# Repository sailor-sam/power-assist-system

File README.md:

# power-assist-system
Electronic servo motor system designed to assist people with severe  disabilities to control the helm and sail sheeting systems of a small  sailboat, via a sip&amp;puff or medical joystick interface.

Kevin and Rick Mercer

https://youtu.be/U6-sZrs9T38?si=PjePZXyoL59SkXcZ&t=115

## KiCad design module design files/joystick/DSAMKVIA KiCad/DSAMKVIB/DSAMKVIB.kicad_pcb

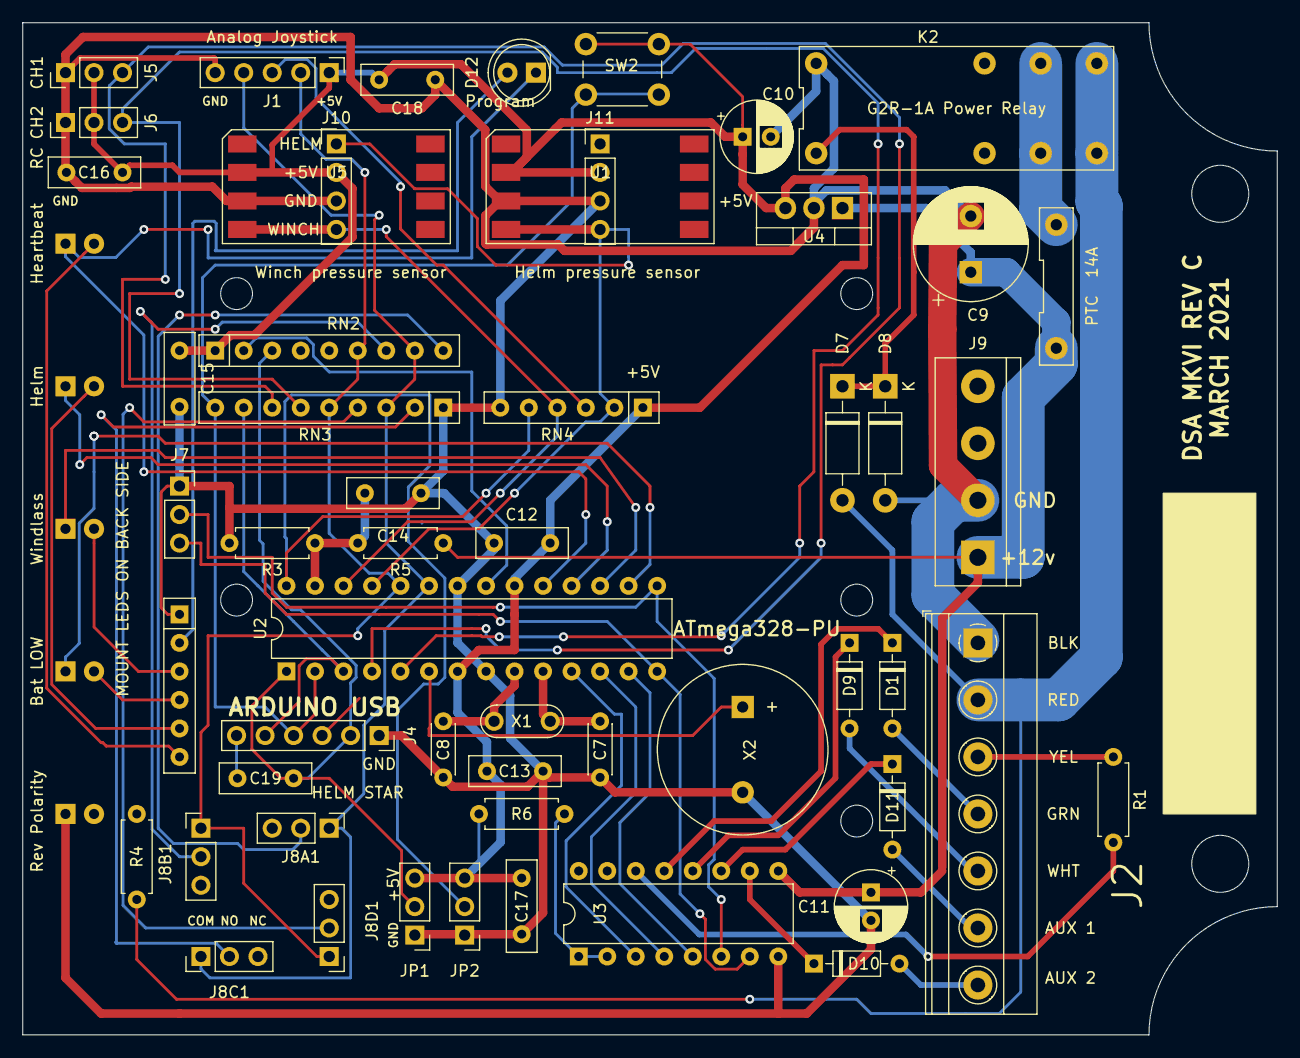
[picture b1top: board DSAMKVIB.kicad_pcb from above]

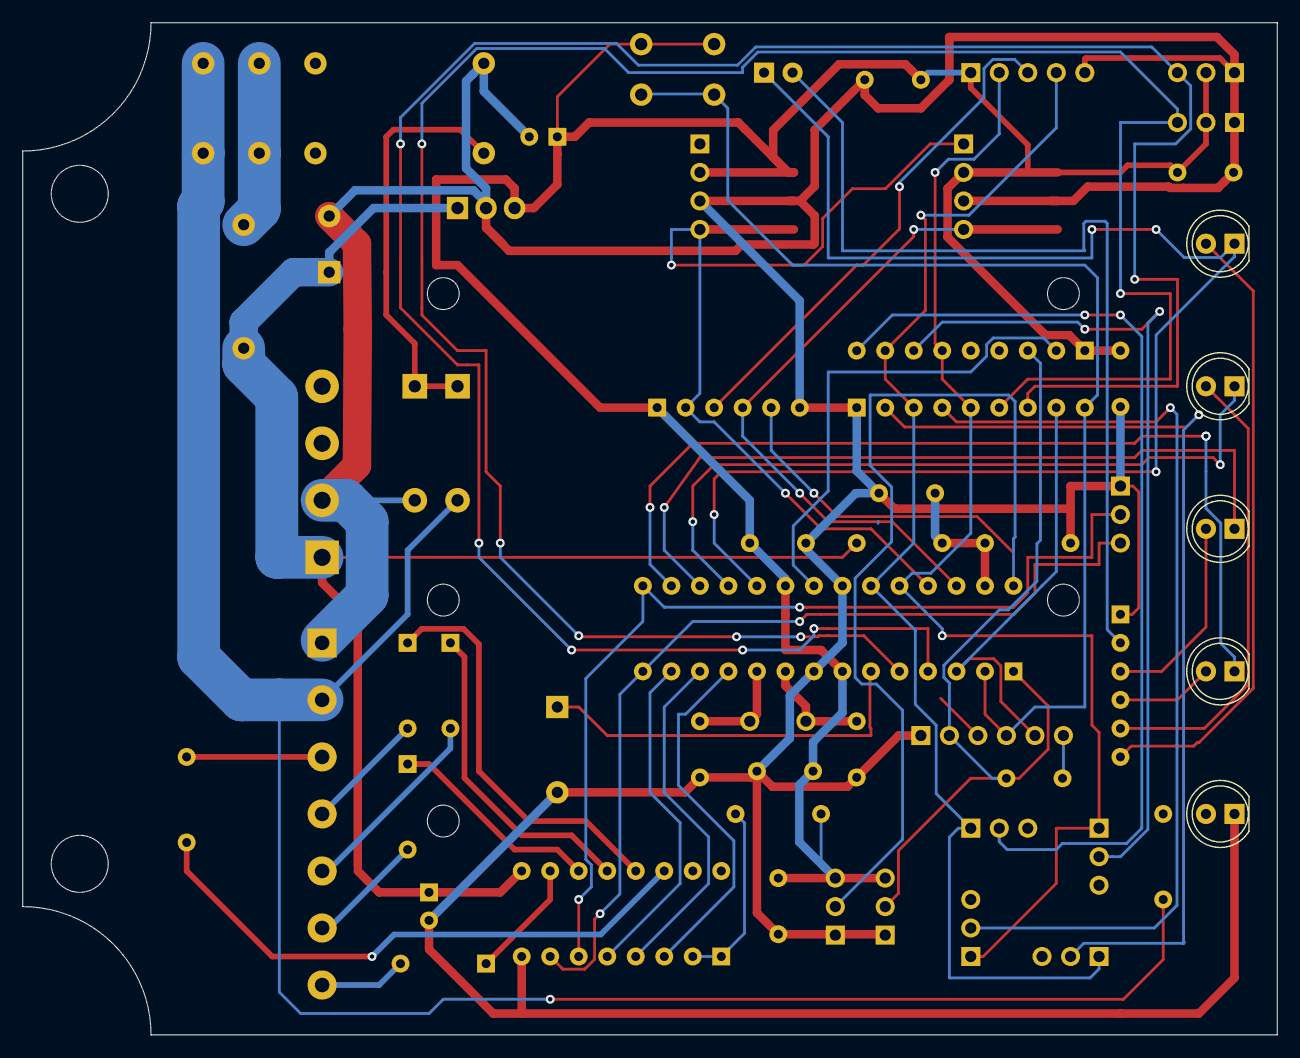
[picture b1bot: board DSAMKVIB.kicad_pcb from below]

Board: 2 copper layers, 111.8 x 90.2 mm, 59 parts (5 on the bottom side), 53 nets.

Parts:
C7, C8: 22 pF; C_Disc_D4.3mm_W1.9mm_P5.00mm
C9: 1000 uF 16V; CP_Radial_D10.0mm_P5.00mm
C10: 10 uF 16V; CP_Radial_D6.3mm_P2.50mm
C11: 10uF 16V; CP_Radial_D6.3mm_P2.50mm
C12, C13, C15, C16, C17, C18: .47uF 50V; C_Disc_D8.0mm_W2.5mm_P5.00mm
C14: 4N7; C_Disc_D8.0mm_W2.5mm_P5.00mm
C19: .1uF 50V; C_Disc_D8.0mm_W2.5mm_P5.00mm
D1, D9, D10, D11: BAT48RL; D_DO-35_SOD27_P7.62mm_Horizontal
D2: Heartbeat; LED_D5.0mm
D3: Helm; LED_D5.0mm
D4: Windlass; LED_D5.0mm
D5: Bat LOW; LED_D5.0mm
D6: Rev Polarity; LED_D5.0mm
D7, D8: 1N4001; D_DO-41_SOD81_P10.16mm_Horizontal
D12: Program LED; LED_D5.0mm
F1: PTC 14A; PTC14
J1: Analog Joystick; PinHeader_1x05_P2.54mm_Vertical
J2: .200 EURO; TerminalBlock_Phoenix_MKDS-1,5-7-5.08_1x07_P5.08mm_Horizont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
J4: USB; PinSocket_1x06_P2.54mm_Vertical
J5: CH1; PinHeader_1x03_P2.54mm_Vertical
J6: CH2; PinHeader_1x03_P2.54mm_Vertical
J7: Cytron PWM; PinSocket_1x03_P2.54mm_Vertical
J8A1: HELM STAR; PinHeader_1x03_P2.54mm_Vertical
J8B1: WINCH IN; PinHeader_1x03_P2.54mm_Vertical
J8C1: HELM PORT; PinHeader_1x03_P2.54mm_Vertical
J8D1: WINCH OUT; PinHeader_1x03_P2.54mm_Vertical
J9: Cytron Pwr; TerminalBlock_bornier-4_P5.08mm
J10: S&P WINCH; PinHeader_1x04_P2.54mm_Vertical
J11: S&P HELM; PinHeader_1x04_P2.54mm_Vertical
JP1: Jumper_CTS; PinHeader_1x03_P2.54mm_Vertical
JP2: Jumper_MODE; PinHeader_1x03_P2.54mm_Vertical
K2: G2R-1A Power Relay; G2R-1A
R1: 470R; R_Axial_DIN0207_L6.3mm_D2.5mm_P7.62mm_Horizontal
R3: 4.9K; R_Axial_DIN0207_L6.3mm_D2.5mm_P7.62mm_Horizontal
R4: 1K; R_Axial_DIN0207_L6.3mm_D2.5mm_P7.62mm_Horizontal
R5: 11K; R_Axial_DIN0207_L6.3mm_D2.5mm_P7.62mm_Horizontal
R6: 10K; R_Axial_DIN0207_L6.3mm_D2.5mm_P7.62mm_Horizontal
RN1: 470R; R_Array_SIP6
RN2, RN3: 10K; R_Array_SIP9
RN4: 100K DIVIDER; R_Array_SIP6
SW2: Program; SW_PUSH_6mm_H4.3mm
U1: Helm pressure sensor; MPXV7007
U2: ATmega328-PU; DIP-28_W7.62mm
U3: ULN2003; DIP-16_W7.62mm
U4: L7805; TO-220-3_Vertical
U5: Winch pressure sensor; MPXV7007
X1: 16 mhz xtal; Resonator-2Pin_W7.0mm_H2.5mm
X2: Buzzer; Buzzer_15x7.5RM7.6

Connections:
+5V: C10.1, C12.1, C13.1, C15.1, C16.1, C17.1, C18.1, J1.1, J4.3, J5.2, J6.2, J10.2, J11.2, JP1.3, JP2.3, R6.1, RN2.1, RN4.1, SW2.1, U1.2, U2.7, U2.20, U4.3, U5.2
+12V: C9.1, C11.1, F1.1, J9.1, R5.1, U3.9, U4.1
+BATT: D7.2, J2.2, K2.4, K2.5, R4.1
CH1: J5.3, RN3.7, U2.4
CH2: J6.3, RN3.6, U2.5
GNDREF: C7.2, C8.2, C9.2, C10.2, C11.2, C12.2, C13.2, C14.2, C15.2, C16.2, C17.2, C18.2, D6.1, D8.2, J1.5, J2.1, J4.1, J5.1, J6.1, J7.1, J9.2, J10.3, J11.3, JP1.1, JP2.1, K2.8, R3.2, RN1.1, RN3.1, RN4.6, U1.3, U2.8, U2.22, U3.8, U4.2, U5.3, X2.2
unnamed: C7.1, U2.10, X1.1
unnamed: C8.1, U2.9, X1.2
unnamed: C14.1, R3.1, R5.2, U2.27
unnamed: C19.1, J4.2, JP1.2, RN2.3, U2.1
unnamed: C19.2, J4.6
unnamed: D1.1, U3.13
unnamed: D1.2, J2.4
unnamed: D2.2, RN1.6
unnamed: D3.1, U2.18
unnamed: D3.2, RN1.5
unnamed: D4.1, U2.17
unnamed: D4.2, RN1.3
unnamed: D5.1, U2.16
unnamed: D5.2, RN1.4
unnamed: D6.2, R4.2
unnamed: D7.1, D8.1, K2.1
unnamed: D9.1, U3.12
unnamed: D9.2, J2.5
unnamed: D10.1, U3.10
unnamed: D10.2, J2.7
unnamed: D11.1, U3.11
unnamed: D11.2, J2.6
unnamed: D2.1, D12.1, U2.19
unnamed: D12.2, RN1.2
unnamed: F1.2, K2.3, K2.6
unnamed: J1.2, J8B1.1, J8D1.1, RN2.6, RN3.5, U2.24
unnamed: J1.3, RN4.3
unnamed: J1.4, J8A1.1, J8C1.1, RN2.8, RN3.3, U2.23
unnamed: J2.3, R1.1
unnamed: J4.4, RN3.9, SW2.2, U2.2
unnamed: J4.5, RN3.8, U2.3
unnamed: J7.2, U2.15, U3.6
unnamed: J7.3, U2.14, U3.7
unnamed: J8A1.2, RN2.9
unnamed: J8B1.2, RN2.7
unnamed: J8C1.2, RN3.2
unnamed: J8D1.2, RN3.4
unnamed: J10.1, J11.4, RN4.2, U1.4, U2.25
unnamed: J10.4, RN4.4, U2.26, U5.4
unnamed: JP2.2, RN4.5, U2.28
unnamed: R1.2, U3.14
unnamed: R6.2, U3.1, U3.2
unnamed: RN2.2, U2.21
unnamed: U2.6, X2.1
unnamed: U2.11, U3.3
unnamed: U2.12, U3.4
unnamed: U2.13, U3.5

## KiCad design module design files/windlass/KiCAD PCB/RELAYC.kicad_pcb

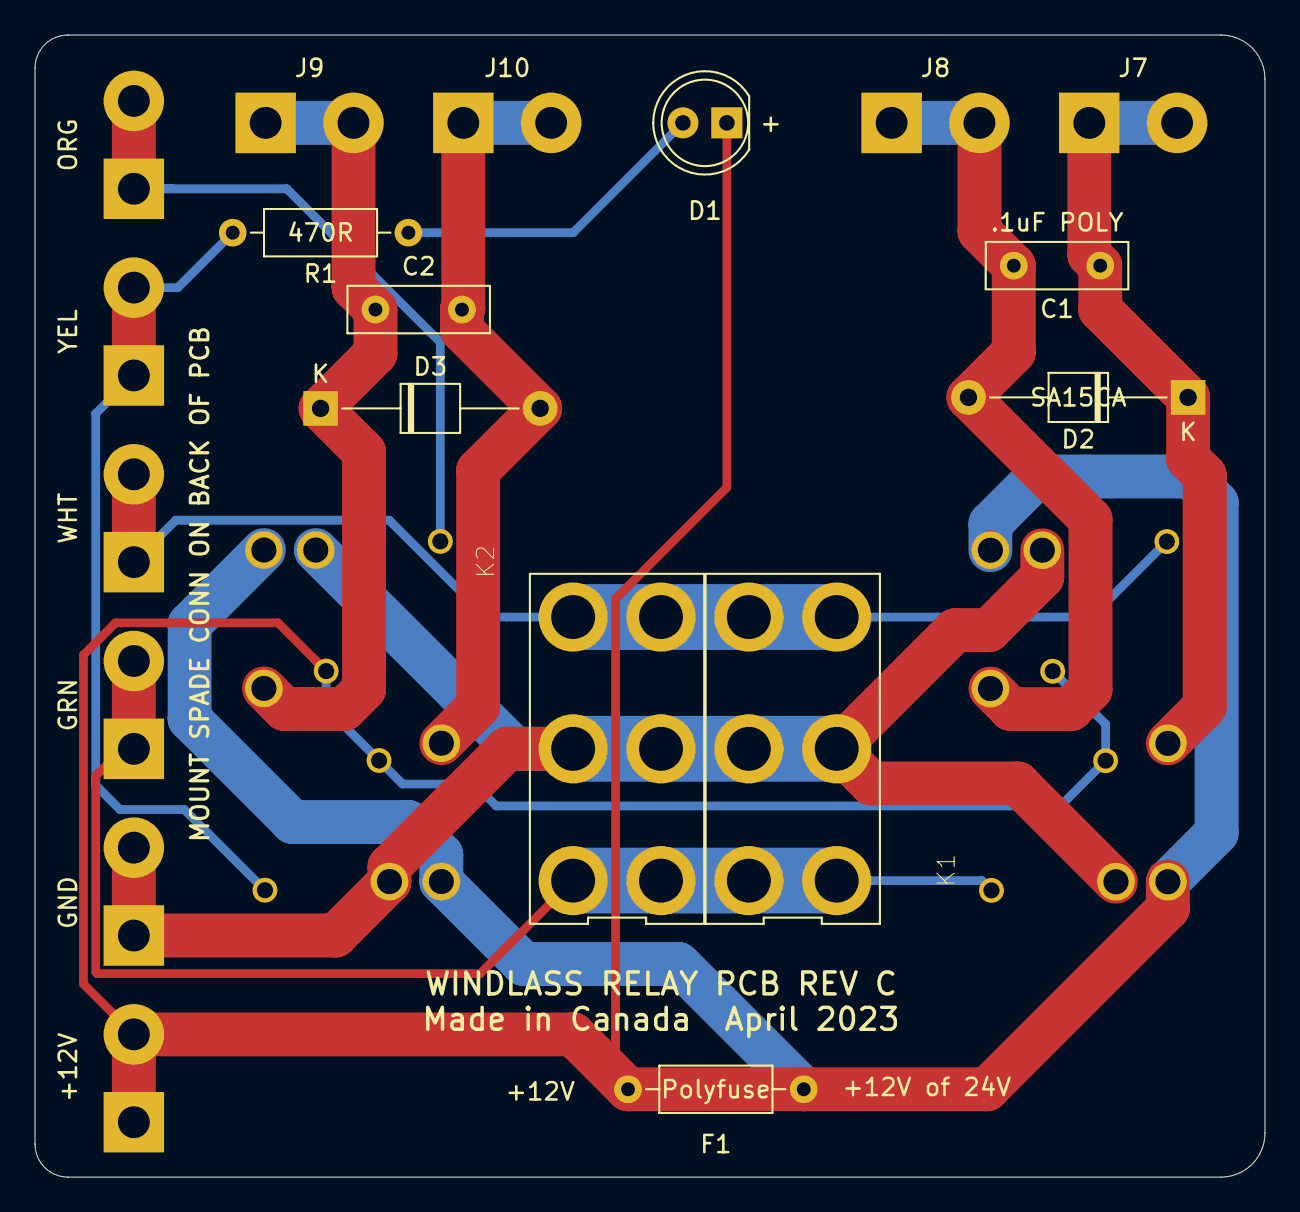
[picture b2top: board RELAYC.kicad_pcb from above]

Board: 2 copper layers, 71.1 x 66.0 mm, 21 parts (0 on the bottom side), 11 nets.

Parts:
C1, C2: .1uF POLY; C_Disc_D8.0mm_W2.5mm_P5.00mm
D1: LED; LED_D5.0mm
D2, D3: SA15CA; D_T-1_P12.70mm_Horizontal
F1: Polyfuse; R_Axial_DIN0207_L6.3mm_D2.5mm_P10.16mm_Horizontal
J1: +12V; 250spadeconn
J2: GND; 250spadeconn
J3: GRN; 250spadeconn
J4: WHT; 250spadeconn
J5: YEL; 250spadeconn
J6: ORG; 250spadeconn
J7, J9: A; 250spadeconn
J8, J10: B; 250spadeconn
K1, K2: V23086 relay; RELAY_V23086C2001A403
R1: 470R; R_Axial_DIN0207_L6.3mm_D2.5mm_P10.16mm_Horizontal
SW1, SW1B1: SW_DPDT_x2; DPDT_SW

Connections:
+12V: D1.1, F1.1, F1.2, J1.1, K1.11, K1.13, K1.21, K1.23, K2.11, K2.13, K2.21, K2.23
GNDREF: J2.1, K1.15, K1.25, K2.15, K2.25, SW1.2, SW1B1.2
unnamed: C1.1, D2.1, J7.1, K1.24
unnamed: C1.2, D2.2, J8.1, K1.14
unnamed: C2.1, D3.1, J9.1, K2.24
unnamed: C2.2, D3.2, J10.1, K2.14
unnamed: D1.2, R1.1
unnamed: J3.1, K1.22, SW1.1, SW1B1.1
unnamed: J4.1, K1.12, SW1.3, SW1B1.3
unnamed: J5.1, K2.12, R1.2
unnamed: J6.1, K2.22

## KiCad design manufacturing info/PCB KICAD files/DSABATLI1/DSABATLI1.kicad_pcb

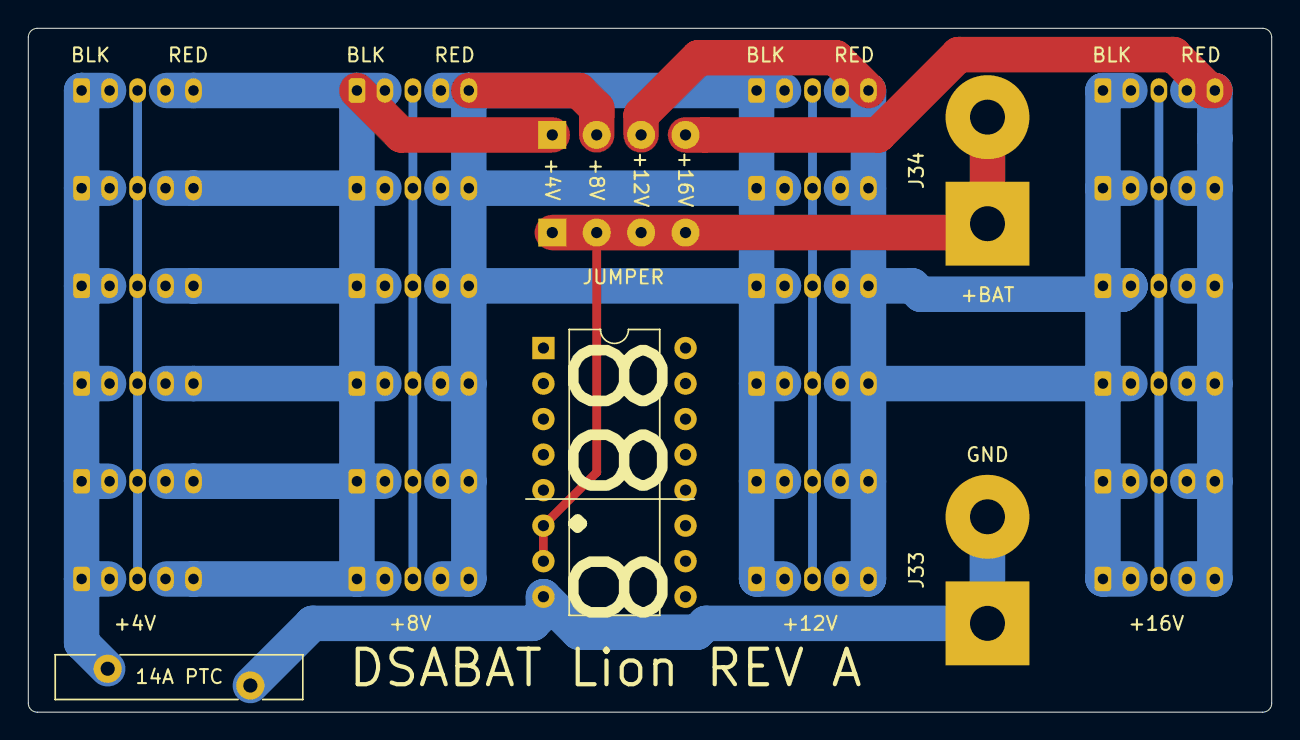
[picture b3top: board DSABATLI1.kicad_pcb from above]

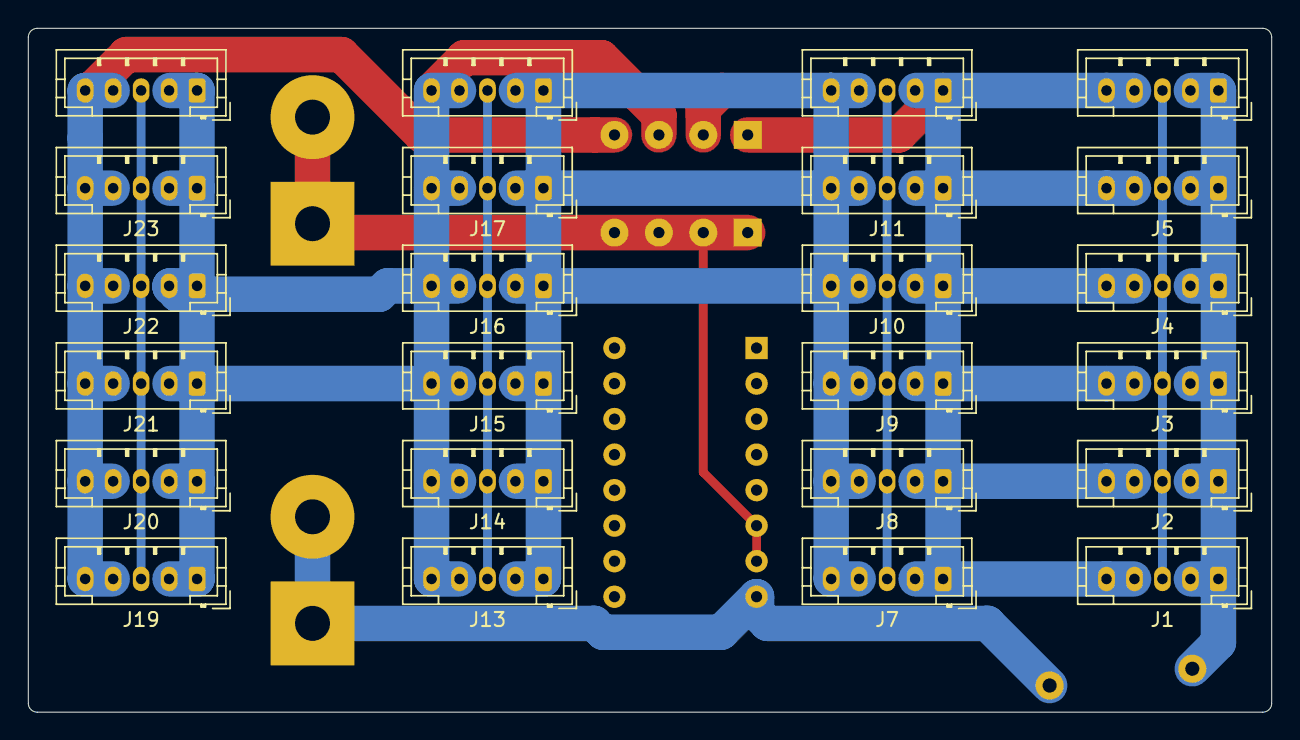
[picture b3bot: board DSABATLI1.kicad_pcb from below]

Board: 2 copper layers, 88.9 x 48.9 mm, 30 parts (24 on the bottom side), 11 nets.

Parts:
14A PTC: Polyfuse; Fuse_Bourns_MF-RHT1000
J1, J2, J3, J4, J5, J6, J7, J8, J9, J10, J11, J12, J13, J14, J15, J16, J17, J18, J19, J20, J21, J22, J23, J24: JST-PHR 5; JST_PH_B5B-PH-K_1x05_P2.00mm_Vertical
J30: .; SolderWirePad_1x04_P3.175mm_Drill0.8mm
J31: +bus; SolderWirePad_1x04_P3.175mm_Drill0.8mm
J33: GND; SolderWirePad_1x02_P7.62mm_Drill2.5mm
J34: +BAT; SolderWirePad_1x02_P7.62mm_Drill2.5mm
U1: VOLTMETER; DIP-16_W10.16mm

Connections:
unnamed: 14A PTC.1, J33.1, J33.2, U1.8
unnamed: 14A PTC.2, J1.1, J1.2, J2.1, J2.2, J3.1, J3.2, J4.1, J4.2, J5.1, J5.2, J6.1, J6.2
unnamed: J1.3, J2.3, J3.3, J4.3, J5.3, J6.3
unnamed: J1.4, J1.5, J2.4, J2.5, J3.4, J3.5, J4.4, J4.5, J5.4, J5.5, J6.4, J6.5, J7.1, J7.2, J8.1, J8.2, J9.1, J9.2, J10.1, J10.2, J11.1, J11.2, J12.1, J12.2, J30.1
unnamed: J7.3, J8.3, J9.3, J10.3, J11.3, J12.3
unnamed: J7.4, J7.5, J8.4, J8.5, J9.4, J9.5, J10.4, J10.5, J11.4, J11.5, J12.4, J12.5, J13.1, J13.2, J14.1, J14.2, J15.1, J15.2, J16.1, J16.2, J17.1, J17.2, J18.1, J18.2, J30.2
unnamed: J13.3, J14.3, J15.3, J16.3, J17.3, J18.3
unnamed: J13.4, J13.5, J14.4, J14.5, J15.4, J15.5, J16.4, J16.5, J17.4, J17.5, J18.4, J18.5, J19.1, J19.2, J20.1, J20.2, J21.1, J21.2, J22.1, J22.2, J23.1, J23.2, J24.1, J24.2, J30.3
unnamed: J19.3, J20.3, J21.3, J22.3, J23.3, J24.3
unnamed: J19.4, J19.5, J20.4, J20.5, J21.4, J21.5, J22.4, J22.5, J23.4, J23.5, J24.4, J24.5, J30.4
unnamed: J31.1, J31.2, J31.3, J31.4, J34.1, J34.2, U1.6, U1.7

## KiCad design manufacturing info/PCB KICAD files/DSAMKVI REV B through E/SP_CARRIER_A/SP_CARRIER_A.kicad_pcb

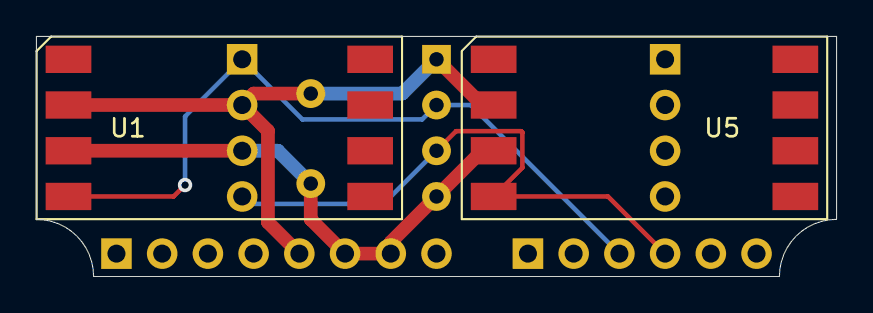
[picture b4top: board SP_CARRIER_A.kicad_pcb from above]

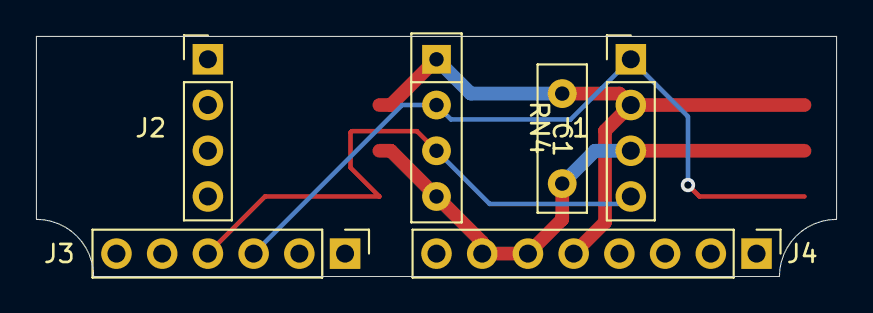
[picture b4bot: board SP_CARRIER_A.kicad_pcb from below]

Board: 2 copper layers, 44.5 x 13.3 mm, 8 parts (6 on the bottom side), 4 nets.

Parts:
C1: 47uF 50V; C_Disc_D8.0mm_W2.5mm_P5.00mm
J1: PIN HEADER; PinHeader_1x04_P2.54mm_Vertical
J2: NO FUNCTION; PinHeader_1x04_P2.54mm_Vertical
J3: ARDUINO ANALOG; PinHeader_1x06_P2.54mm_Vertical
J4: ARDUINO POWER; PinHeader_1x08_P2.54mm_Vertical
RN4: 100K DIVIDER; R_Array_SIP4
U1: HELM PRESSURE SENSOR; MPXV7007
U5: WINCH PRESSURE SENSOR; MPXV7007

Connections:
unnamed: C1.1, J1.2, J4.5, RN4.1, U1.2, U5.2
unnamed: C1.2, J1.3, J4.6, J4.7, RN4.4, U1.3, U5.3
unnamed: J1.1, J3.3, RN4.2, U1.4
unnamed: J1.4, J3.4, RN4.3, U5.4

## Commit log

2023-11-03 initial upload
2023-11-04 File structure clean-up
    General reorganization and clean-up of file structure and file names. No file content changed
2023-11-25 clean up with Meister S
